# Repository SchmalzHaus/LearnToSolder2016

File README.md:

# LearnToSolder2016

## Introduction

For the past couple years, Deanna Schmalz has designed a simple circuit board which we then use to teach learn to solder classes. We  make enough boards and buy enough parts to teach all of the 4th graders at Glen Lake Elementary School in Minnetonka Minnesota, USA how to solder. 

This site contains all of the information related to this year's Learn To Solder board. If you want to learn more about how to solder, if you want to know what you need to purchase so you can solder at home, or if you want to make more of these boards for yourself or your organization, this site has everything you'll need.

If you want to reach Brian Schmalz (brian@schmalzaus.com) or Deanna (deanna@schmalzhaus.com) to ask us any questions, please do so. 

This same board design was used at our booth at the 2016 MSP Mini Maker Faire, with one small change in the silk screen text. If you got a board from us at the Maker Faire, all of this information applies as well.

All text files and designs on this site are Open Source. You are free to use these files and do whatever you wish with them.

## LearnToSolder 2016 Kit Contents

* Qty 1 Bare Circuit Board (see above image for back and front views of the bare board)
* Qty 2 Switches
* Qty 2 Blinking LEDs
* Qty 1 Battery Holder
* Qty 1 Battery

## Tools

To solder electronic kits together, you will need (at a minimum)

### Soldering Iron

We do not recommend buying a soldering iron unless it is 'temperature controlled'. This means you get to set the tip temperature with a knob or buttons, and the iron will only heat up as much as it needs to in order to maintain that temperature. Using a non-temp controlled iron has, in our experience, led to lots of frustration and failed kits.

This is the iron we recommend, as we've had great experience with it and it is very inexpensive : [http://www.hobbyking.com/hobbyking/store/__19240__Soldering_Station_with_Adjustable_Heat_Range_US_Warehouse_.html]

You can also by this same type of iron from many other places, including Amazon and Ebay, but the price tends to be a bit higher. Some of the companies listed below under Other Soldering Kits also sell tools like irons.

### Solder

For beginners, we strongly recommend using leaded solder (rather than lead-free). The safety risk is very minimal (just be sure to wash your hands with soap when you are done) and it is far, far easier to get good soldered joints with leaded solder when you're just starting to learn soldering. You can buy leaded electronic solder at many on-line stores like SparkFun [https://www.sparkfun.com/products/9161] or Adafruit [https://www.adafruit.com/products/1886]. Make sure to buy 60/40 or 63/37 (those numbers represent the ratio of tin to lead in the solder) electronic solder - there are other solders out there (like silver solder for jewelry for example) that won't work for electronics.

### Brass Sponge

When you buy your iron, buy a bras sponge if the iron doesn't already come with it. These are much better than the watter sponge that comes with the iron for cleaning the tip of the soldering iron.

### Wire Cutter

All of the companies listed below sell small wire cutters, or you can get them locally at hardware stores too. The best kind is something that will allow you to cut off wires flush with the board - sometimes called 'flush cutters'. For example [https://www.sparkfun.com/products/11952] or [https://www.adafruit.com/products/152]

### Other tools

There are lots of other tools you can get to help you while solder. Third-hands can be very useful. Needle nose pliers, solder suckers, magnifying glasses, solder wick, wire strippers, etc.

## Kit Assembly Process (overview)

There are only a couple steps to assembling this kit, as it is very simple. If you have done soldering before, you can just walk through this overview of the steps to complete your kit. If you want to learn more about how to do the actual soldering of a joint, the following websites and resources will give you plenty of background materials and explanations:

https://learn.sparkfun.com/tutorials/how-to-solder---through-hole-soldering

http://www.howtogeek.com/63630/how-to-use-a-soldering-iron-a-beginners-guide/

https://cdn-learn.adafruit.com/downloads/pdf/adafruit-guide-excellent-soldering.pdf

### Steps:

1. Insert the two switches into the board. Make sure all parts go into the board from the top side (with the thick white lines) to the back side (with all of the text). The switches snap down into the board - you sometimes have to press them in hard to get them to snap. Solder the four pins of each switch.

2. Insert the two LEDs. Long wires go into square holes. You sometimes have to wiggle the LEDs a bit to get them to press all the way flat down on the top side of the board due to a thick spot on the LED leads. Bend the leads apart on the back side to keep the LEDs in place as you solder the LED wires on the back side of the board.

3. Insert the battery holder to the front of the board, being careful to align the outline of the battery hold to the white outline on the top of the board (there is a square tab on the battery holder than needs to match up to the square tab part of the outline). While holding the battery holder into the board, flip it over and solder both pins.

4. Insert the battery into the holder, flat shiny side up. Press the buttons to see your LEDs light. If you hold down a button, it's LED will begin to cycle through different colors and begin to blink.

You can follow the path of the electricity by looking at the thick white line on the top side of the board, or the thinner copper wires on the back side of the board. (They mirror each other.) 

## Other Soldering Kits

There are SO MANY kits available today, it's impossible to list all of them, or even the good ones. If you do a Google search for "electronic soldering kit" you will find lots of them out there. Some are easier than others, and some come with great instructions (and some don't).

We buy a lot of high quality soldering kits from the following on-line companies:

Evil Mad Scientist [http://shop.evilmadscientist.com/]
* Their Boldport Buggy is excellent [http://shop.evilmadscientist.com/]
* The Flickery Flame is a great beginner kit [http://shop.evilmadscientist.com/productsmenu/793]

Spark Fun Electronics [https://www.sparkfun.com/]
* They have a whole catagory of 'kits', some of which are soldering kits [https://www.sparkfun.com/categories/157]
* The SparkFun Simon Says - Through-Hole kit is really fun [https://www.sparkfun.com/products/10547]

Adafruit [https://www.adafruit.com/]
* The Drawdio is quite fun [https://www.adafruit.com/categories/28]
* Their Minty Boost is actually quite useful [https://www.adafruit.com/products/14]

SeeedStudio [http://www.seeedstudio.com/]
* Their 4-Soldering Zoo Kit looks super cute [https://www.seeedstudio.com/item_detail.html?p_id=1950]

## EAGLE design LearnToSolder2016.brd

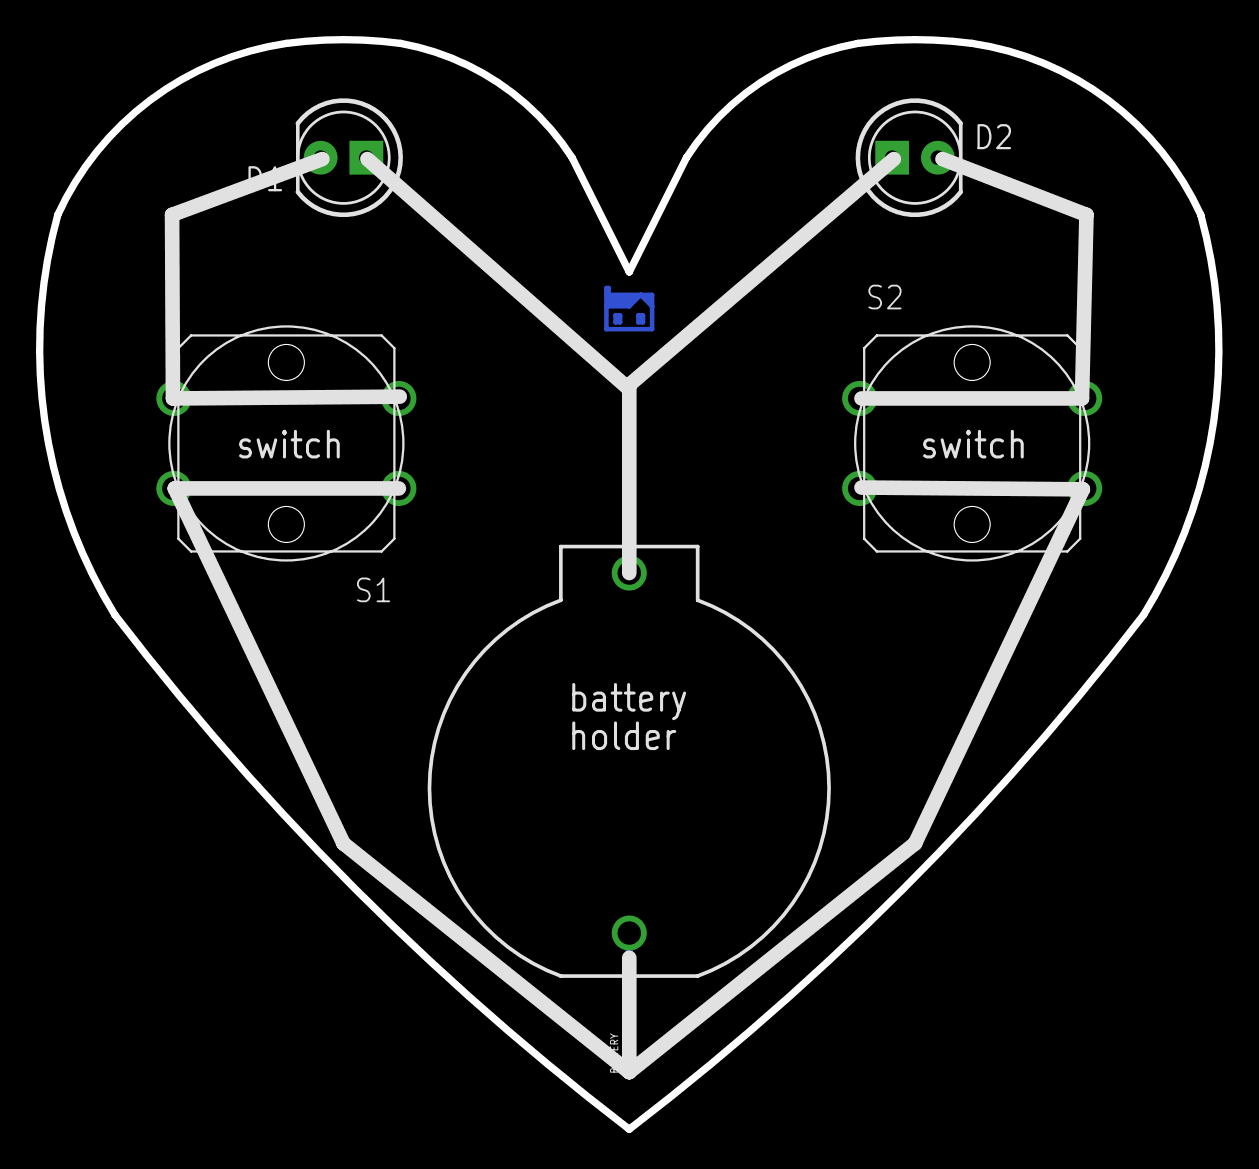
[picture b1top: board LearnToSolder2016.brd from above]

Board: 2 copper layers, 65.5 x 60.5 mm, 6 parts (1 on the bottom side), 4 nets.

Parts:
BATTERY: BATTCOM_20MM_PTH
D1, D2: LED5MM
S1, S2: SWITCH_SPST; OMRON-12MMX12MM_SPST-B3F-4000
U$3: SCHMALZHAUSSCHMALZHAUS_SMALL; SCHMALZHAUS_SMALL

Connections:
unnamed: D1.K, S1.1, S1.2
unnamed: D2.K, S2.3, S2.4
unnamed: BATTERY.2, S1.3, S1.4, S2.1, S2.2
unnamed: BATTERY.1, D1.A, D2.A

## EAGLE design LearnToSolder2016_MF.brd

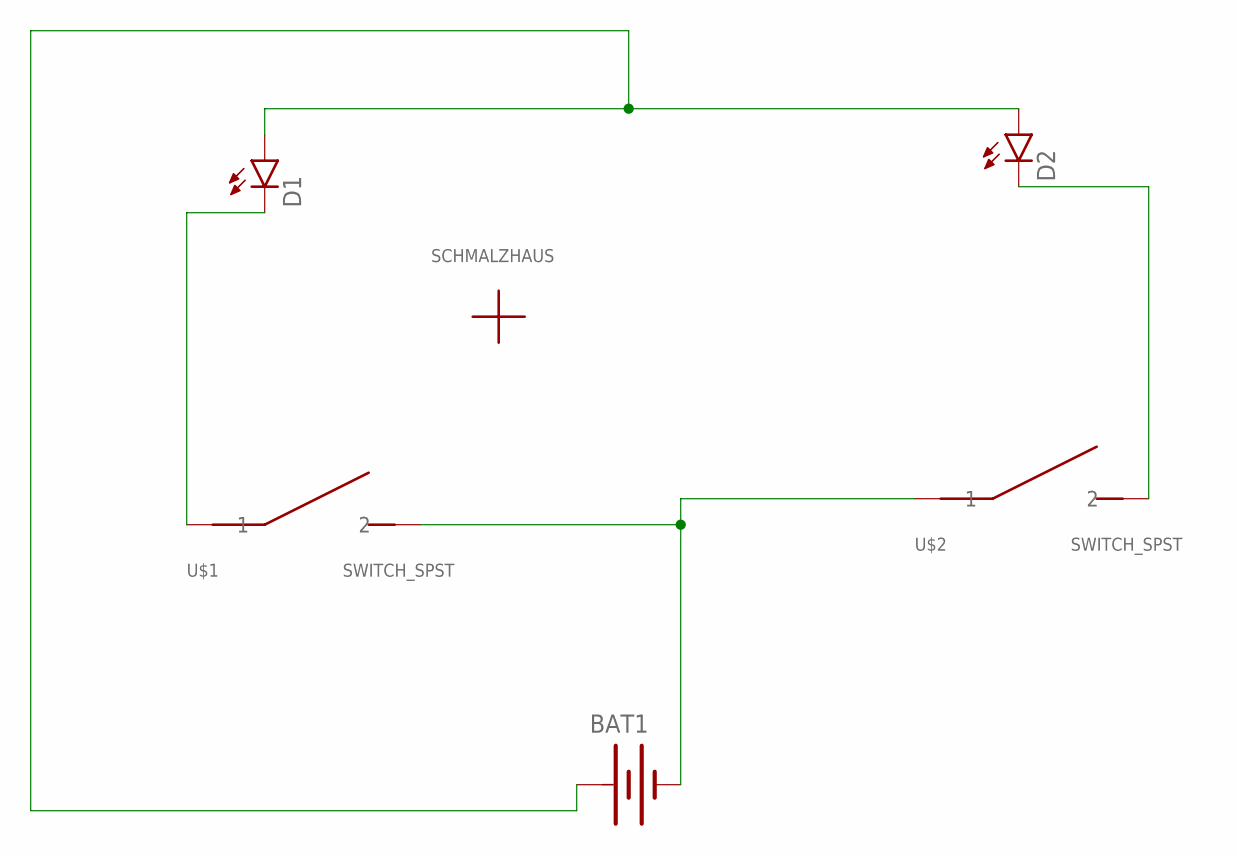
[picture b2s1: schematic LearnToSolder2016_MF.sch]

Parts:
BAT1: BATTERY20PTH; BATTCOM_20MM_PTH
D1, D2: LED5MM
U$1, U$2: SWITCH_SPST; OMRON-12MMX12MM_SPST-B3F-4000
U$3: SCHMALZHAUSSCHMALZHAUS_SMALL; SCHMALZHAUS_SMALL

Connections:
unnamed: D1.K (C), U$1.1, U$1.2 (1)
unnamed: D2.K (C), U$2.3 (2), U$2.4 (2)
unnamed: BAT1.2 (-), U$1.3 (2), U$1.4 (2), U$2.1, U$2.2 (1)
unnamed: BAT1.1 (+), D1.A, D2.A

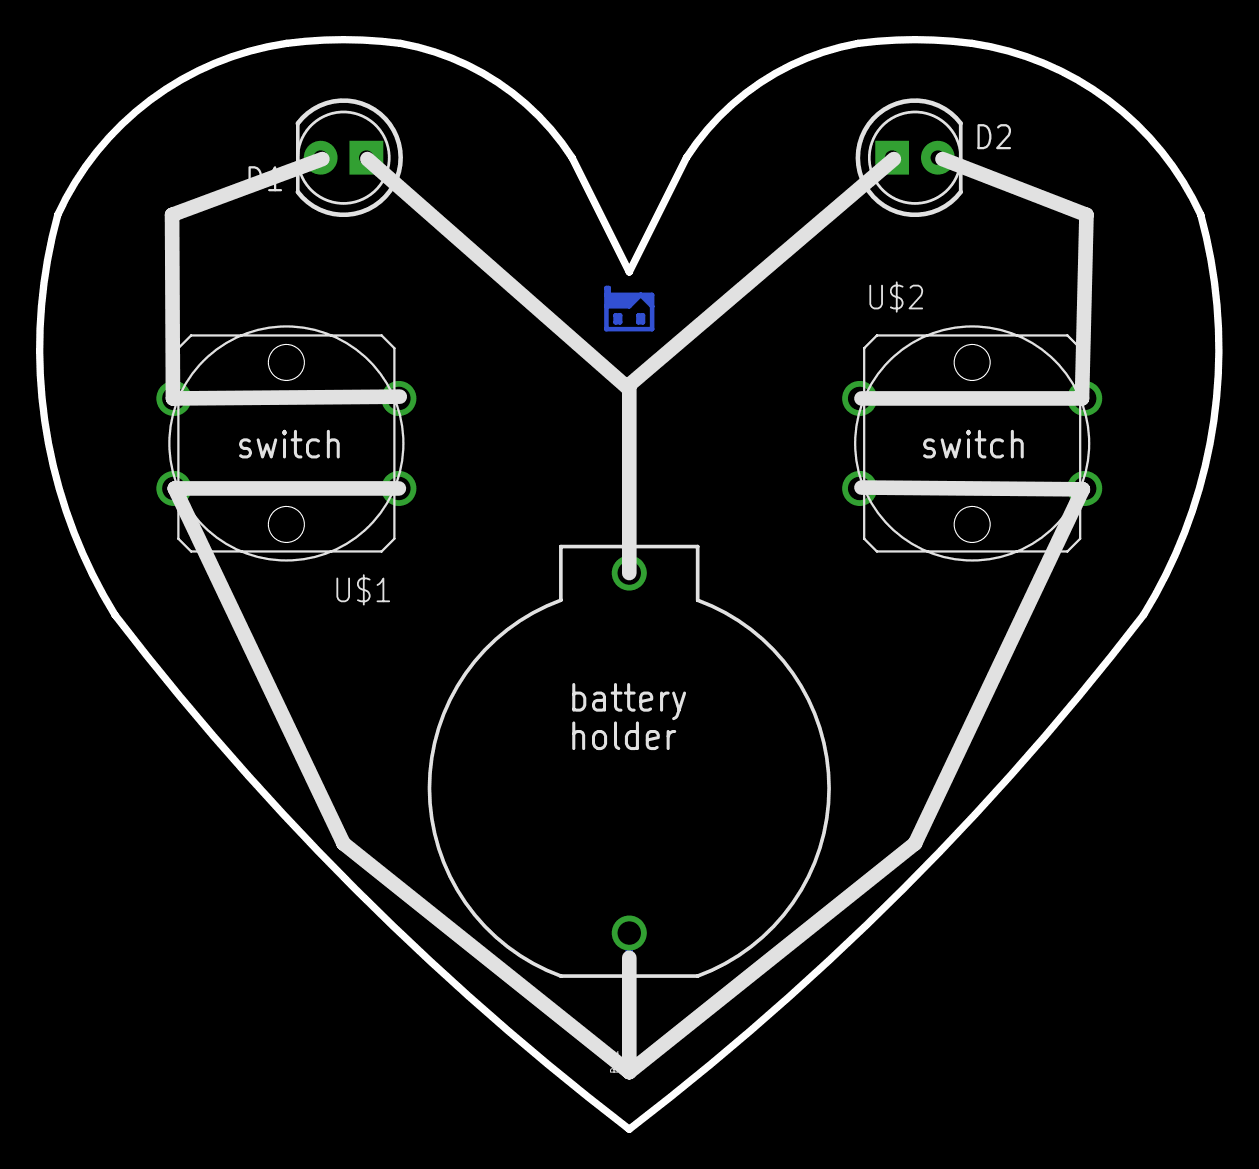
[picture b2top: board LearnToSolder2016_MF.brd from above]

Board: 2 copper layers, 65.5 x 60.5 mm, 6 parts (1 on the bottom side), 4 nets.

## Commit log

2016-04-13 Got library pretty much done.
2016-04-17 Finished board design, created MakerFaire version, created gerbers.
2016-05-21 Minor update to schematic - just moved symbols around so it would fit better on a screen.
2016-05-22 Added images for Readme file.
2016-07-07 Added kit assembly steps
2018-03-18 Fixed spelling
